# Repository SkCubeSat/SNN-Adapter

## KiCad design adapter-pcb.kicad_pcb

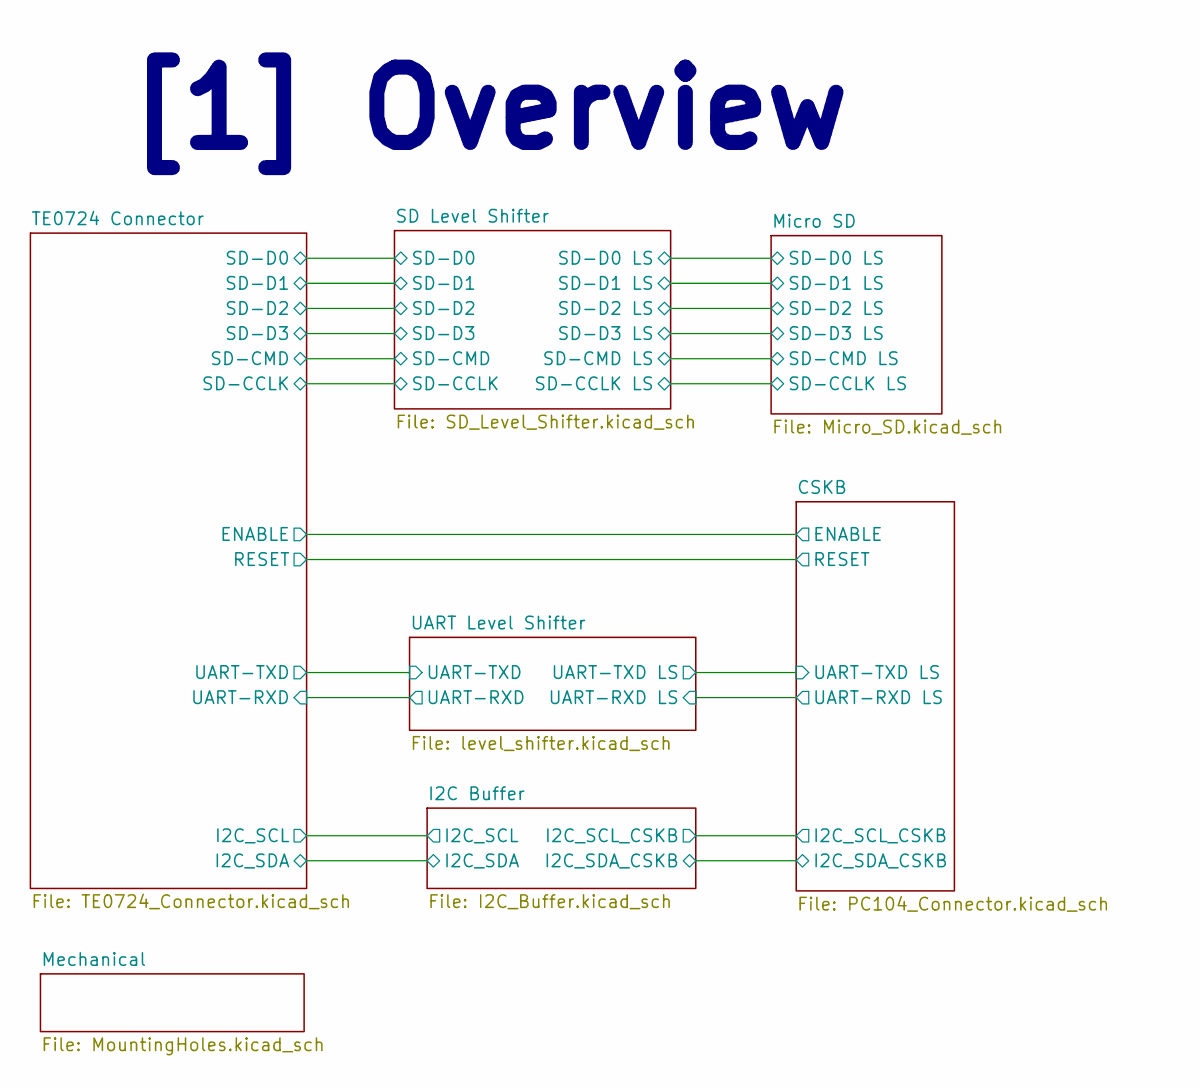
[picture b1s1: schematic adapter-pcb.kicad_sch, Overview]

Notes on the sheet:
[1] Overview

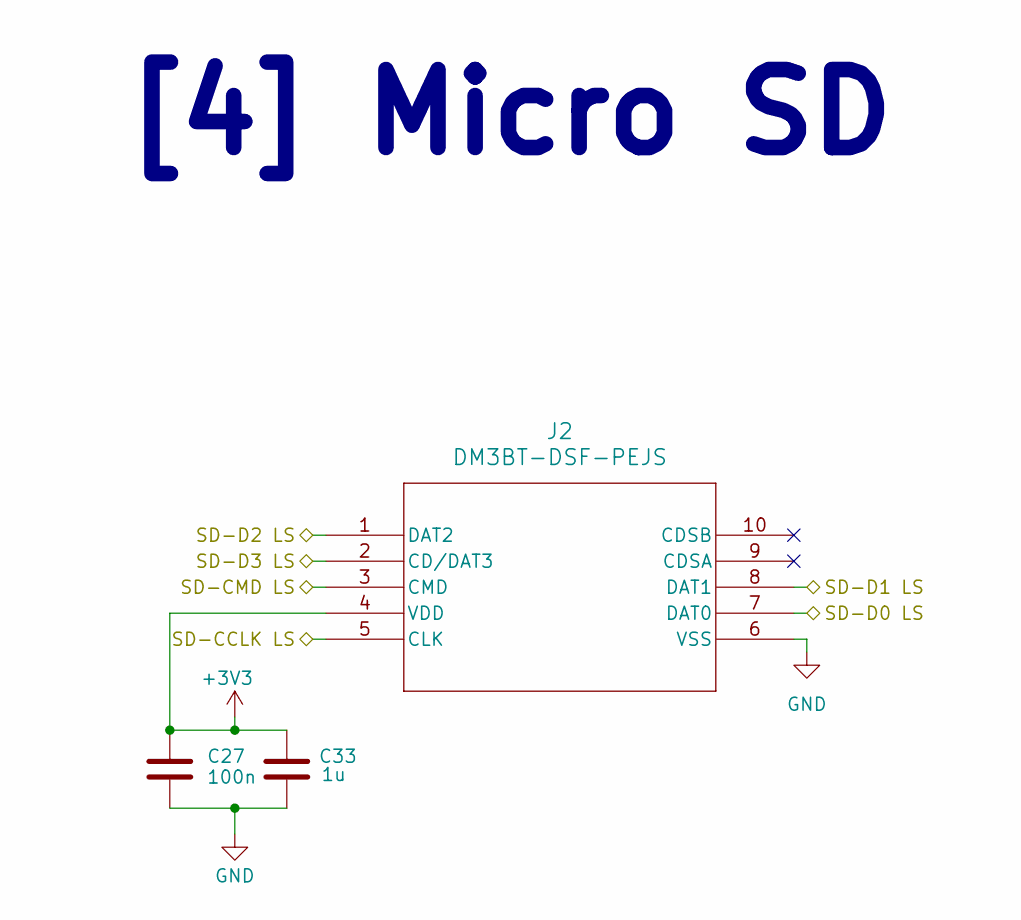
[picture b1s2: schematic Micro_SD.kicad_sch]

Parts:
C27: 100n; C_0603_1608Metric; MPN GCM188R71H104KA57J
C33: 1u; C_0805_2012Metric; MPN GCM21BR71H105KA03L
J2: DM3BT-DSF-PEJS; DM3BT_DSF_PEJS; MPN DM3BT-DSF-PEJS

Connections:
+3V3: C27.1, C33.1, J2.4 (VDD); also elsewhere on the board
/Micro SD/SD-CCLK LS: J2.5 (CLK); also elsewhere on the board
/Micro SD/SD-CMD LS: J2.3 (CMD); also elsewhere on the board
/Micro SD/SD-D0 LS: J2.7 (DAT0); also elsewhere on the board
/Micro SD/SD-D1 LS: J2.8 (DAT1); also elsewhere on the board
/Micro SD/SD-D2 LS: J2.1 (DAT2); also elsewhere on the board
/Micro SD/SD-D3 LS: J2.2 (CD/DAT3); also elsewhere on the board
GND: C27.2, C33.2, J2.6 (VSS); also elsewhere on the board

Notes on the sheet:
[4] Micro SD

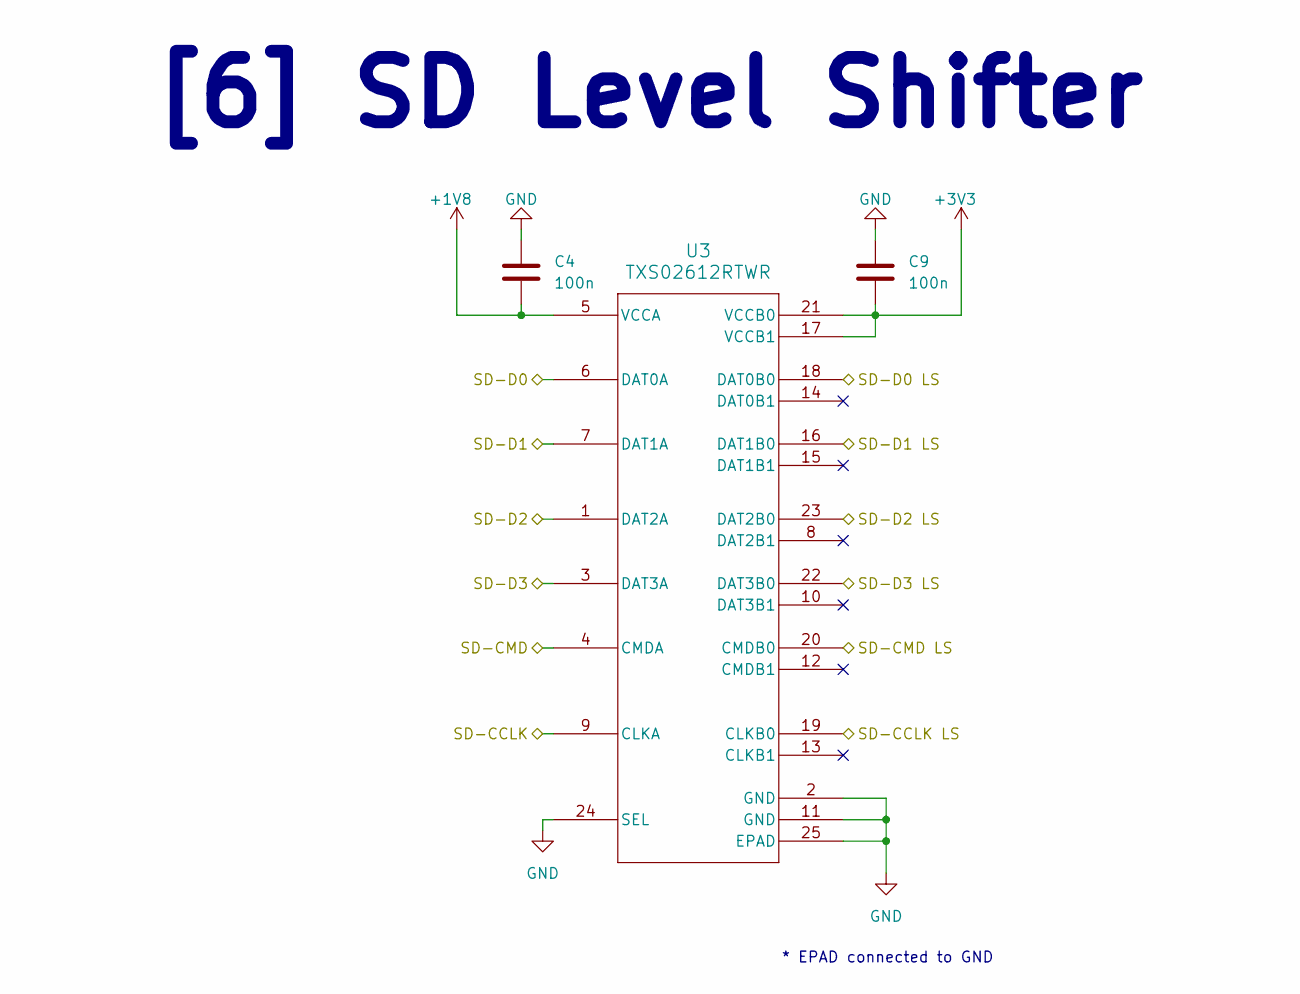
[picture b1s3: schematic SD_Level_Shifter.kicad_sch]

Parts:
C4, C9: 100n; C_0603_1608Metric; MPN GCM188R71H104KA57J
U3: TXS02612RTWR; RTW24_2P45X2P45; MPN TXS02612RTWR

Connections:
+1V8: C4.2, U3.5 (VCCA); also elsewhere on the board
+3V3: C9.2, U3.17 (VCCB1), U3.21 (VCCB0); also elsewhere on the board
/Micro SD/SD-CCLK LS: U3.19 (CLKB0); also elsewhere on the board
/Micro SD/SD-CMD LS: U3.20 (CMDB0); also elsewhere on the board
/Micro SD/SD-D0 LS: U3.18 (DAT0B0); also elsewhere on the board
/Micro SD/SD-D1 LS: U3.16 (DAT1B0); also elsewhere on the board
/Micro SD/SD-D2 LS: U3.23 (DAT2B0); also elsewhere on the board
/Micro SD/SD-D3 LS: U3.22 (DAT3B0); also elsewhere on the board
/SD Level Shifter/SD-CCLK: U3.9 (CLKA); also elsewhere on the board
/SD Level Shifter/SD-CMD: U3.4 (CMDA); also elsewhere on the board
/SD Level Shifter/SD-D0: U3.6 (DAT0A); also elsewhere on the board
/SD Level Shifter/SD-D1: U3.7 (DAT1A); also elsewhere on the board
/SD Level Shifter/SD-D2: U3.1 (DAT2A); also elsewhere on the board
/SD Level Shifter/SD-D3: U3.3 (DAT3A); also elsewhere on the board
GND: C4.1, C9.1, U3.2 (GND), U3.11 (GND), U3.24 (SEL), U3.25 (EPAD); also elsewhere on the board

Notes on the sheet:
[6] SD Level Shifter
* EPAD connected to GND

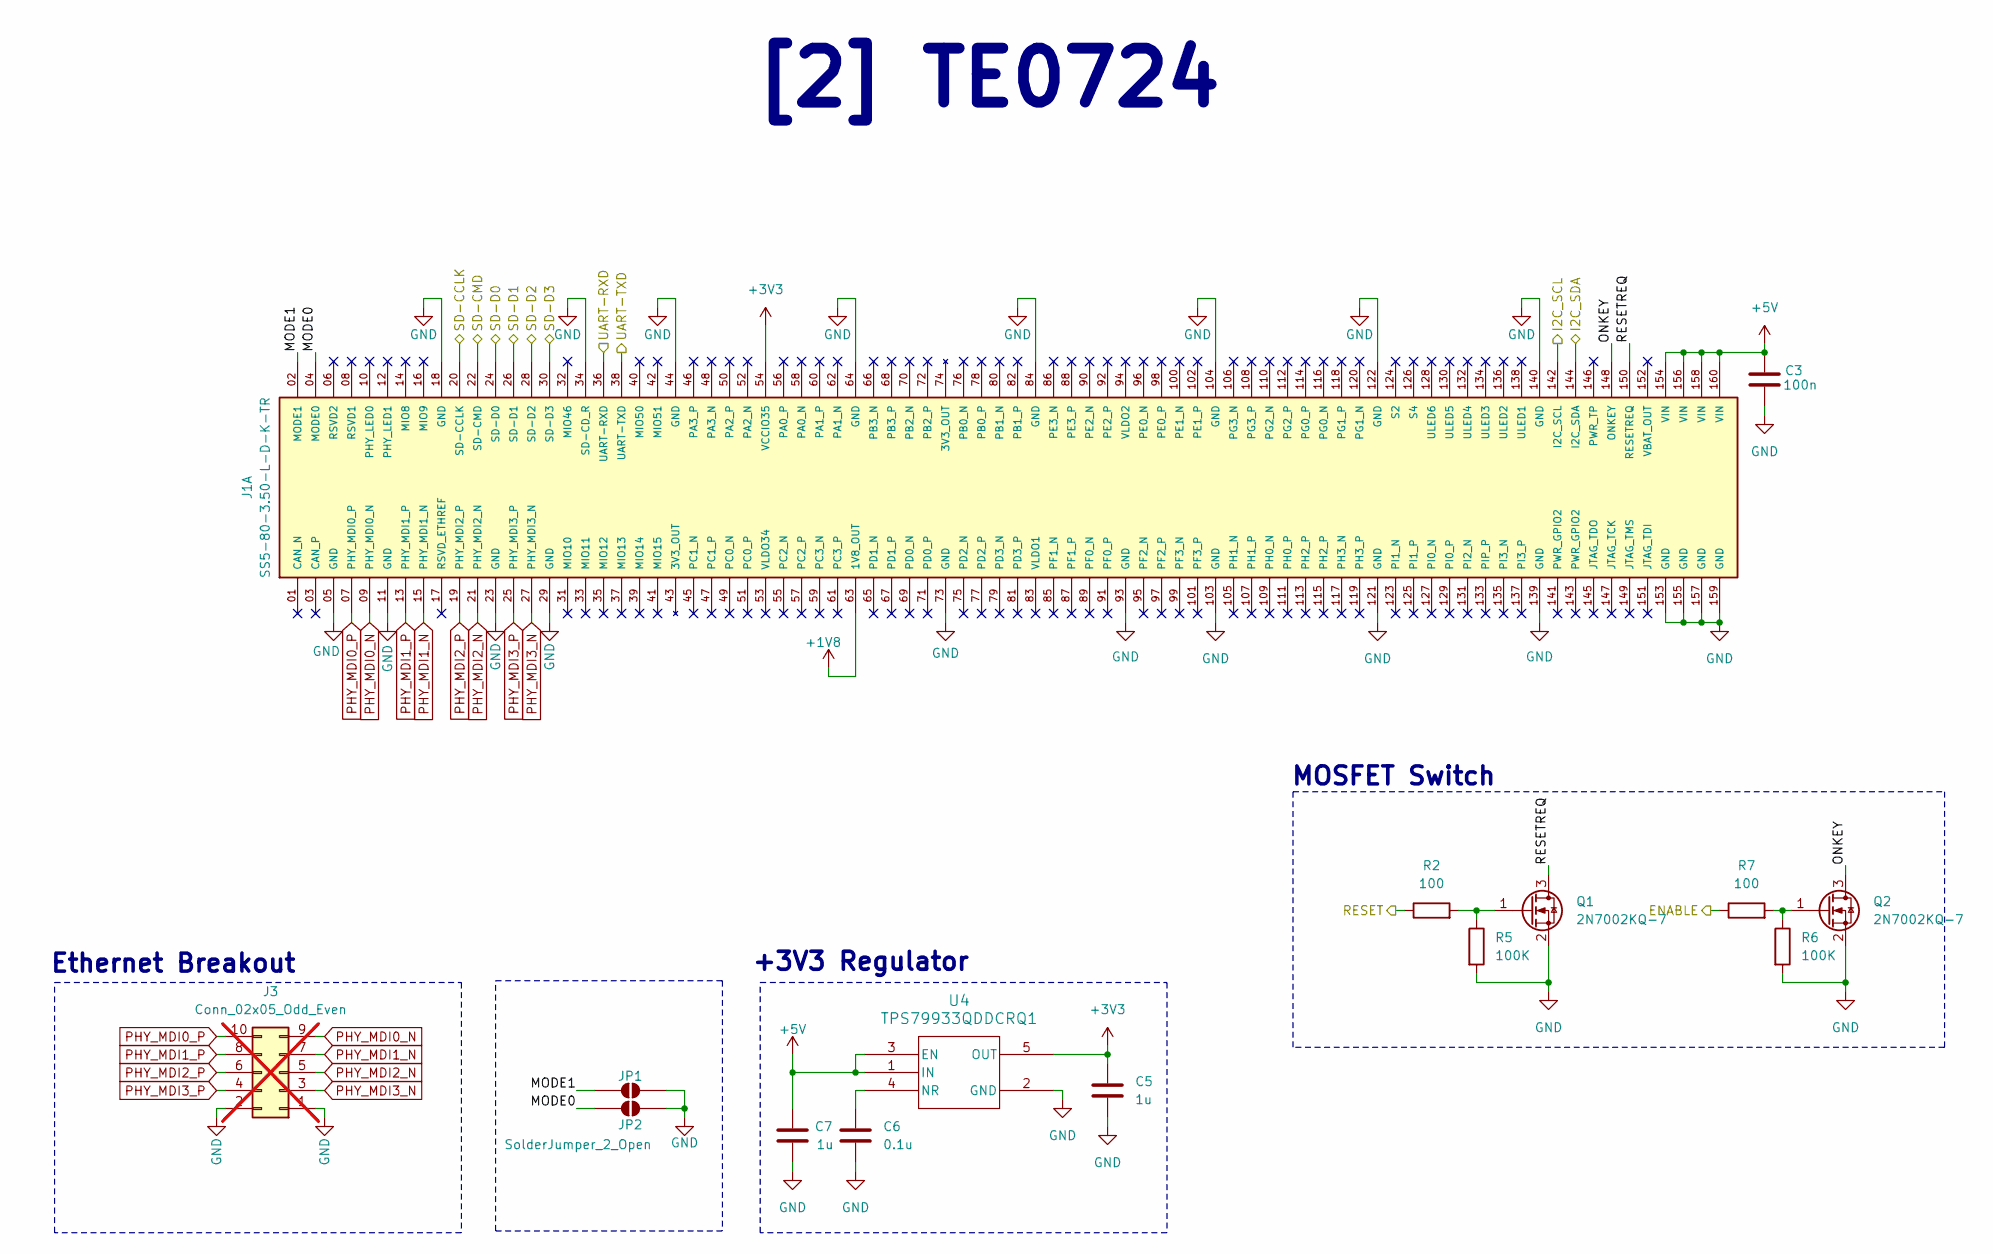
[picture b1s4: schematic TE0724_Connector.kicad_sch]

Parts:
C3: 100n; C_0603_1608Metric; MPN GCM188R71H104KA57J
C5, C7: 1u; C_1206_3216Metric; MPN GCM31MR71H105KA55L
C6: 0.1u; C_0603_1608Metric; MPN GCM188R71H104KA57J
J1: SS5-80-3.50-L-D-K-TR; SAMTEC_SS5-80-3.50-X-D-K-XX; PARTREV F
J3: Conn_02x05_Odd_Even; PinSocket_2x05_P2.54mm_Vertical; not fitted
JP1, JP2: SolderJumper_2_Open; SolderJumper-2_P1.3mm_Open_RoundedPad1.0x1.5mm
Q1, Q2: 2N7002KQ-7; SOT-23; MPN 2N7002KQ-7
R2, R7: 100; R_0402_1005Metric; MPN MCS0402MD1000BE100
R5, R6: 100K; R_0402_1005Metric; MPN MCS0402MD1003BE100
U4: TPS79933QDDCRQ1; DDC5; MPN TPS79933QDDCRQ1

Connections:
+1V8: J1.63 (1V8_OUT); also elsewhere on the board
+3V3: C5.1, J1.54 (VCCIO35), U4.5 (OUT); also elsewhere on the board
+5V: C3.1, C7.1, J1.154 (VIN), J1.156 (VIN), J1.158 (VIN), J1.160 (VIN), U4.1 (IN), U4.3 (EN); also elsewhere on the board
/CSKB/ENABLE: R7.1; also elsewhere on the board
/CSKB/RESET: R2.1; also elsewhere on the board
/I2C Buffer/I2C_SCL: J1.142 (I2C_SCL); also elsewhere on the board
/I2C Buffer/I2C_SDA: J1.144 (I2C_SDA); also elsewhere on the board
/SD Level Shifter/SD-CCLK: J1.20 (SD-CCLK); also elsewhere on the board
/SD Level Shifter/SD-CMD: J1.22 (SD-CMD); also elsewhere on the board
/SD Level Shifter/SD-D0: J1.24 (SD-D0); also elsewhere on the board
/SD Level Shifter/SD-D1: J1.26 (SD-D1); also elsewhere on the board
/SD Level Shifter/SD-D2: J1.28 (SD-D2); also elsewhere on the board
/SD Level Shifter/SD-D3: J1.30 (SD-D3); also elsewhere on the board
/TE0724 Connector/MODE0: J1.04 (MODE0), JP2.1 (A)
/TE0724 Connector/MODE1: J1.02 (MODE1), JP1.1 (A)
/TE0724 Connector/ONKEY: J1.148 (ONKEY), Q2.3 (D)
/TE0724 Connector/RESETREQ: J1.150 (RESETREQ), Q1.3 (D)
/TE0724 Connector/UART-RXD: J1.36 (UART-RXD); also elsewhere on the board
/TE0724 Connector/UART-TXD: J1.38 (UART-TXD); also elsewhere on the board
GND: C3.2, C5.2, C6.2, C7.2, J1.05 (GND), J1.11 (GND), J1.18 (GND), J1.23 (GND), J1.29 (GND), J1.34 (SD-CD_R), J1.44 (GND), J1.64 (GND), J1.73 (GND), J1.84 (GND), J1.93 (GND), J1.103 (GND), J1.104 (GND), J1.121 (GND), J1.122 (GND), J1.139 (GND), J1.140 (GND), J1.153 (GND), J1.155 (GND), J1.157 (GND), J1.159 (GND), J3.1, J3.2, JP1.2 (B), JP2.2 (B), Q1.2 (S), Q2.2 (S), R5.2, R6.2, U4.2 (GND); also elsewhere on the board
unnamed: Q1.1 (G), R2.2, R5.1
unnamed: Q2.1 (G), R6.1, R7.2
unnamed: C6.1, U4.4 (NR)
PHY_MDI0_N: J1.09 (PHY_MDI0_N), J3.9
PHY_MDI0_P: J1.07 (PHY_MDI0_P), J3.10
PHY_MDI1_N: J1.15 (PHY_MDI1_N), J3.7
PHY_MDI1_P: J1.13 (PHY_MDI1_P), J3.8
PHY_MDI2_N: J1.21 (PHY_MDI2_N), J3.5
PHY_MDI2_P: J1.19 (PHY_MDI2_P), J3.6
PHY_MDI3_N: J1.27 (PHY_MDI3_N), J3.3
PHY_MDI3_P: J1.25 (PHY_MDI3_P), J3.4

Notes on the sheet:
+3V3 Regulator
MOSFET Switch
[2] TE0724
Ethernet Breakout

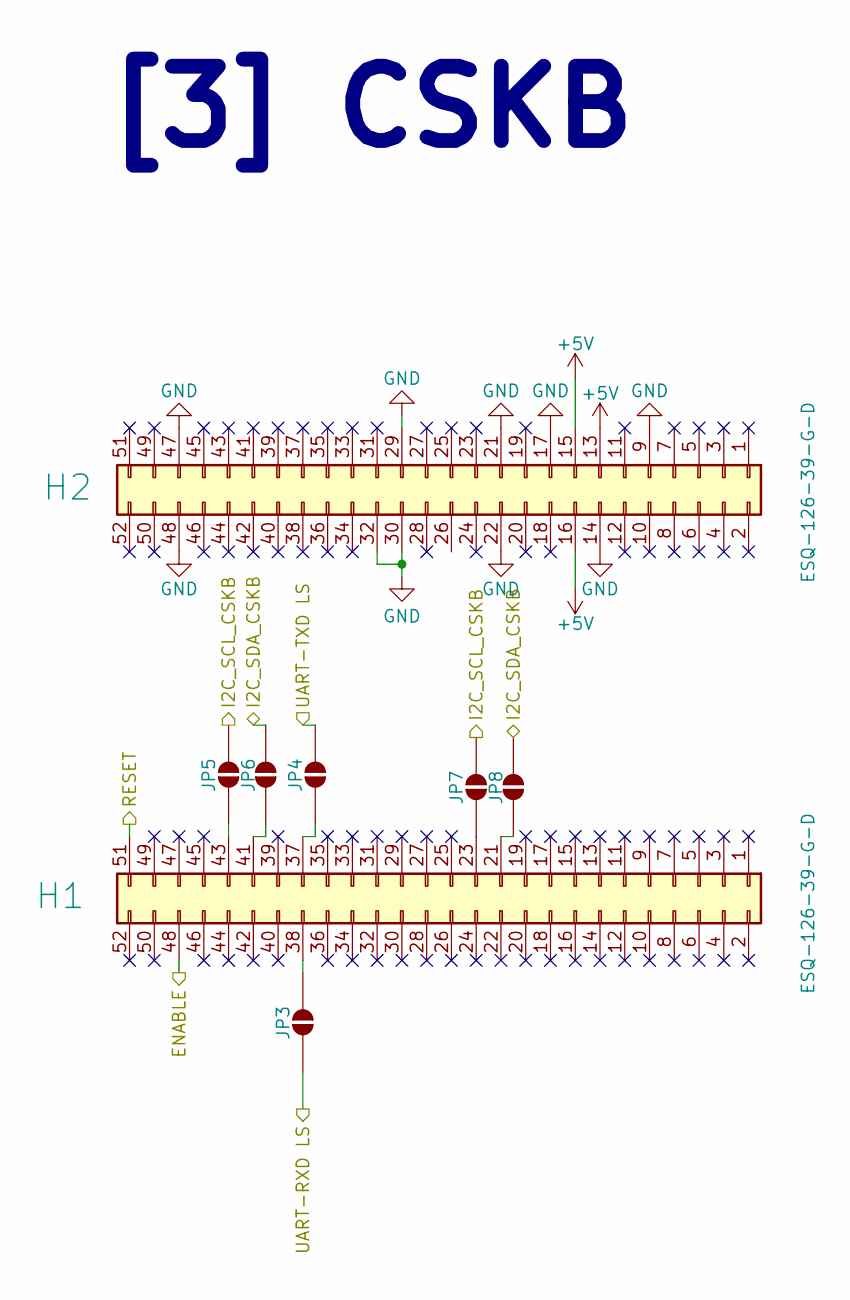
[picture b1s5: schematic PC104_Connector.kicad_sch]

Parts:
H1, H2: ESQ-126-39-G-D; RHDR52W64P254_2X26_6654X495X1135P; MPN ESQ-126-39-G-D
JP3, JP4: SolderJumper_2_Open; SolderJumper-2_P1.3mm_Bridged_RoundedPad1.0x1.5mm
JP5, JP6, JP7, JP8: SolderJumper_2_Open; SolderJumper-2_P1.3mm_Open_RoundedPad1.0x1.5mm

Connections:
+5V: H2.13, H2.15, H2.16; also elsewhere on the board
/CSKB/ENABLE: H1.48; also elsewhere on the board
/CSKB/I2C_SCL_CSKB: JP5.2 (B), JP7.2 (B); also elsewhere on the board
/CSKB/I2C_SDA_CSKB: JP6.2 (B), JP8.2 (B); also elsewhere on the board
/CSKB/RESET: H1.51; also elsewhere on the board
/CSKB/UART-RXD LS: JP3.1 (A); also elsewhere on the board
/CSKB/UART-TXD LS: JP4.2 (B); also elsewhere on the board
GND: H2.9, H2.14, H2.17, H2.21, H2.22, H2.29, H2.30, H2.32, H2.47, H2.48; also elsewhere on the board
unnamed: H1.21, JP8.1 (A)
unnamed: H1.23, JP7.1 (A)
unnamed: H1.37, JP4.1 (A)
unnamed: H1.38, JP3.2 (B)
unnamed: H1.41, JP6.1 (A)
unnamed: H1.43, JP5.1 (A)

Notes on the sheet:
[3] CSKB

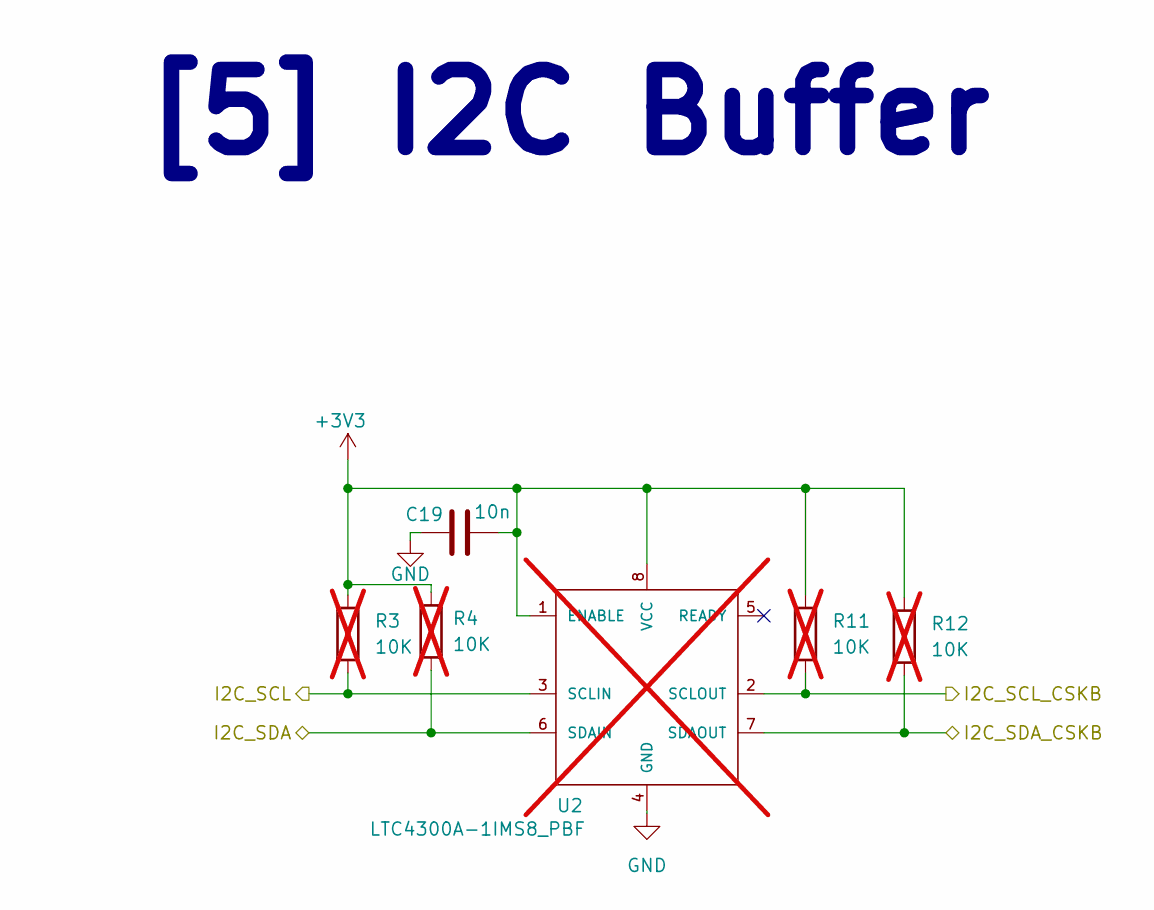
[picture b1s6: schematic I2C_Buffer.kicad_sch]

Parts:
C19: 10n; C_0402_1005Metric; MPN GCM155R71H103KA55J
R3, R4, R11, R12: 10K; R_0402_1005Metric; MPN MCS0402MD1002BE100; not fitted
U2: LTC4300A-1IMS8_PBF; MPN ltc4300a1ims8; not fitted

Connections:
+3V3: C19.2, R3.1, R4.1, R11.1, R12.1, U2.1 (ENABLE), U2.8 (VCC); also elsewhere on the board
/CSKB/I2C_SCL_CSKB: R11.2, U2.2 (SCLOUT); also elsewhere on the board
/CSKB/I2C_SDA_CSKB: R12.2, U2.7 (SDAOUT); also elsewhere on the board
/I2C Buffer/I2C_SCL: R3.2, U2.3 (SCLIN); also elsewhere on the board
/I2C Buffer/I2C_SDA: R4.2, U2.6 (SDAIN); also elsewhere on the board
GND: C19.1, U2.4 (GND); also elsewhere on the board

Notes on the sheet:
[5] I2C Buffer

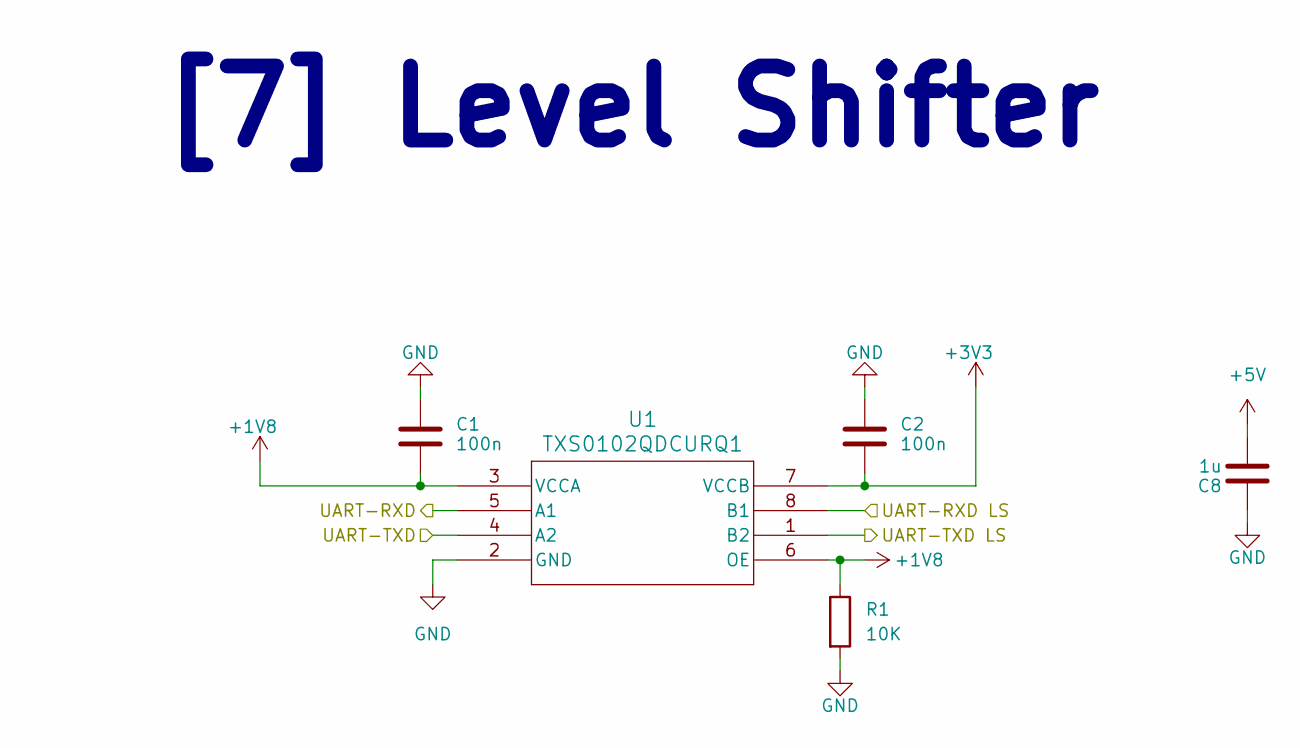
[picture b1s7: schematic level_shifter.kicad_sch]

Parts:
C1, C2: 100n; C_0603_1608Metric; MPN GCM188R71H104KA57J
C8: 1u; C_0603_1608Metric; MPN GCM188R71E105KA64D
R1: 10K; R_0402_1005Metric; MPN MCS0402MD1002BE100
U1: TXS0102QDCURQ1; MPN TXS0102QDCURQ1

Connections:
+1V8: C1.2, R1.1, U1.3 (VCCA), U1.6 (OE); also elsewhere on the board
+3V3: C2.2, U1.7 (VCCB); also elsewhere on the board
+5V: C8.2; also elsewhere on the board
/CSKB/UART-RXD LS: U1.8 (B1); also elsewhere on the board
/CSKB/UART-TXD LS: U1.1 (B2); also elsewhere on the board
/TE0724 Connector/UART-RXD: U1.5 (A1); also elsewhere on the board
/TE0724 Connector/UART-TXD: U1.4 (A2); also elsewhere on the board
GND: C1.1, C2.1, C8.1, R1.2, U1.2 (GND); also elsewhere on the board

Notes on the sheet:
[7] Level Shifter

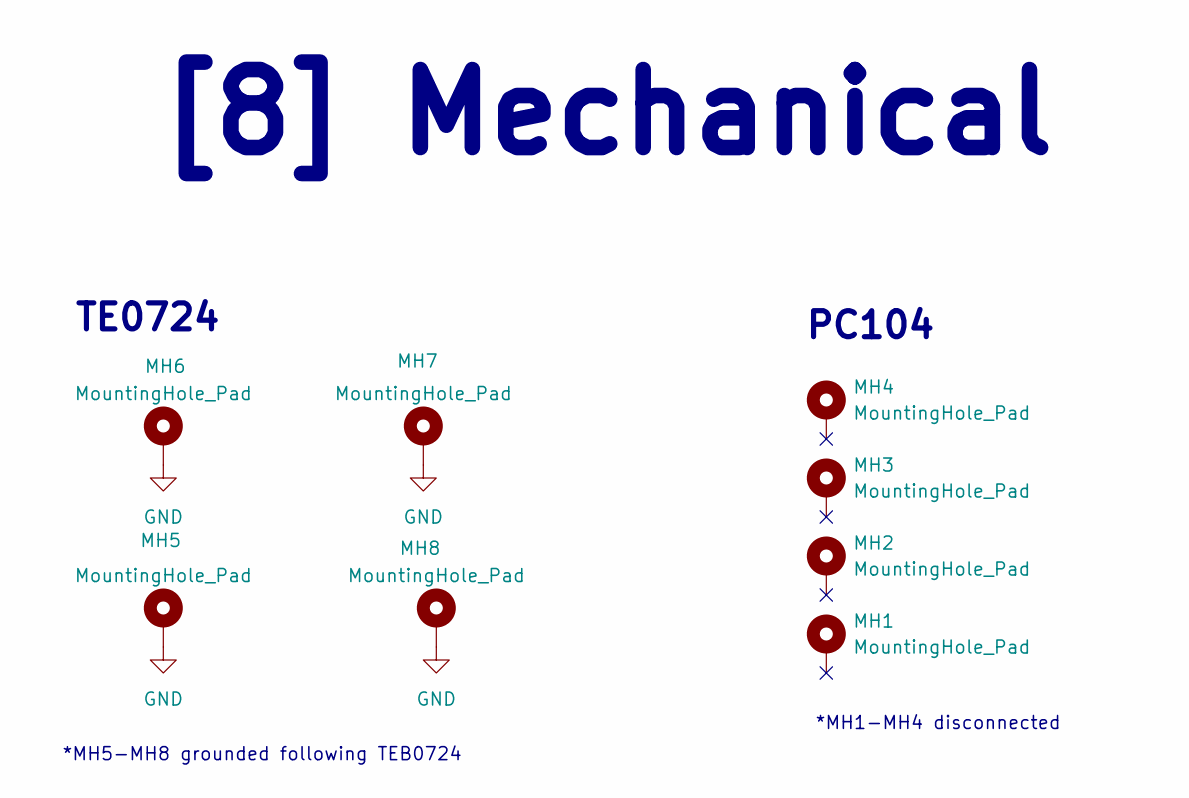
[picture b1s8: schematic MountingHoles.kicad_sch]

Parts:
MH1, MH2, MH3, MH4: MountingHole_Pad; MountingHole_3.18mm_6.35mm_Pad
MH5, MH6, MH7, MH8: MountingHole_Pad; MountingHole_2.2mm_M2_Pad

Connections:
GND: MH5.1 (1_1), MH6.1 (1_1), MH7.1 (1_1), MH8.1 (1_1); also elsewhere on the board

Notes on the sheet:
PC104
*MH1-MH4 disconnected
[8] Mechanical
TE0724
*MH5-MH8 grounded following TEB0724

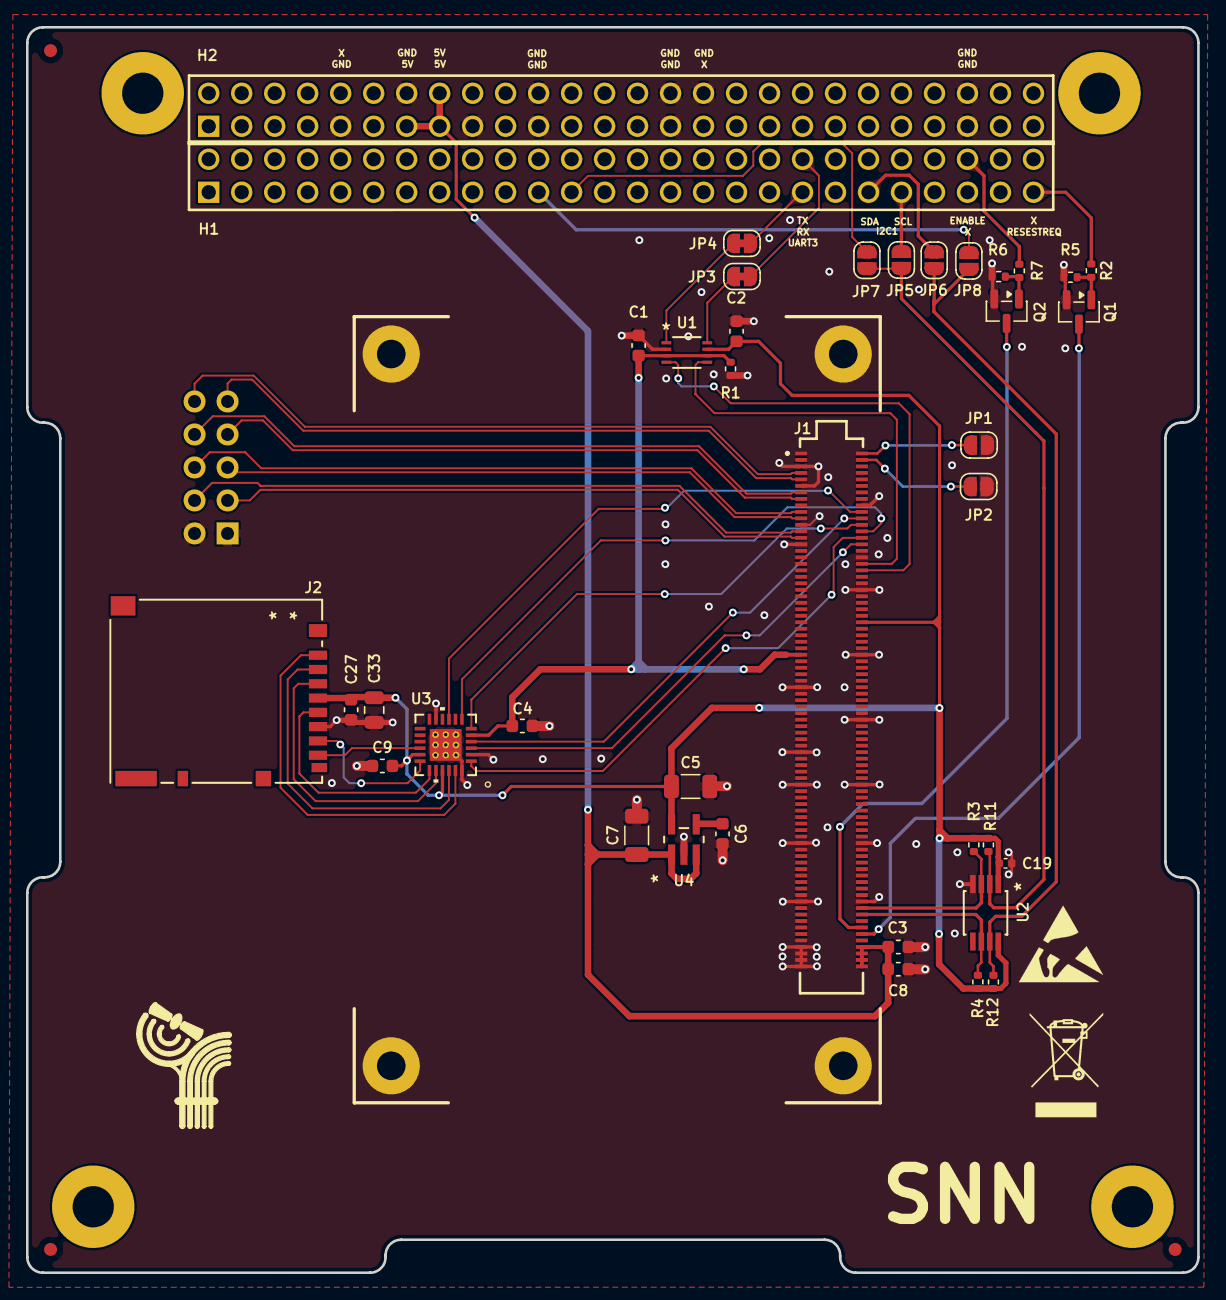
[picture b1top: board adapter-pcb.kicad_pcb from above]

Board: 2 copper layers, 90.2 x 95.9 mm, 48 parts (1 on the bottom side), 47 nets.

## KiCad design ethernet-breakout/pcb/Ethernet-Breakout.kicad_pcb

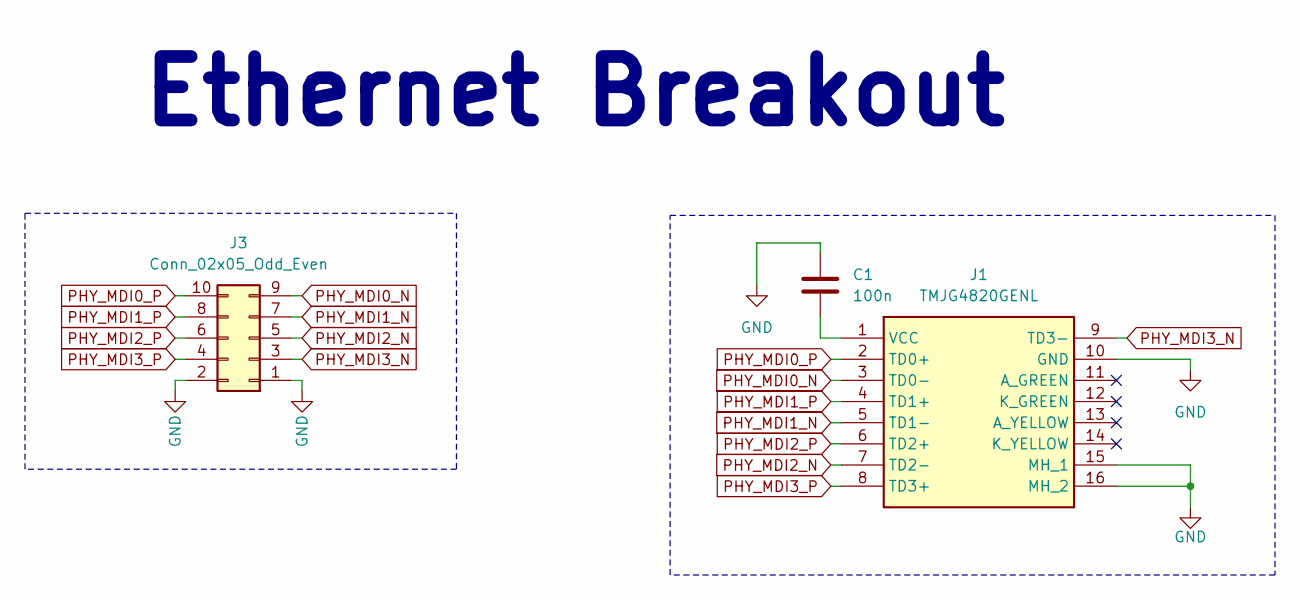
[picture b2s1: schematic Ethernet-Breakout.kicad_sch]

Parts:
C1: 100n; C_Disc_D3.0mm_W1.6mm_P2.50mm
J1: TMJG4820GENL; Mouser Part Number 960-TMJG4820GENL
J3: Conn_02x05_Odd_Even; PinSocket_2x05_P2.54mm_Vertical

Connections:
GND: C1.1, J1.10 (GND), J1.15 (MH_1), J1.16 (MH_2), J3.1, J3.2
unnamed: C1.2, J1.1 (VCC)
PHY_MDI0_N: J1.3 (TD0-), J3.9
PHY_MDI0_P: J1.2 (TD0+), J3.10
PHY_MDI1_N: J1.5 (TD1-), J3.7
PHY_MDI1_P: J1.4 (TD1+), J3.8
PHY_MDI2_N: J1.7 (TD2-), J3.5
PHY_MDI2_P: J1.6 (TD2+), J3.6
PHY_MDI3_N: J1.9 (TD3-), J3.3
PHY_MDI3_P: J1.8 (TD3+), J3.4

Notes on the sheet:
Ethernet Breakout

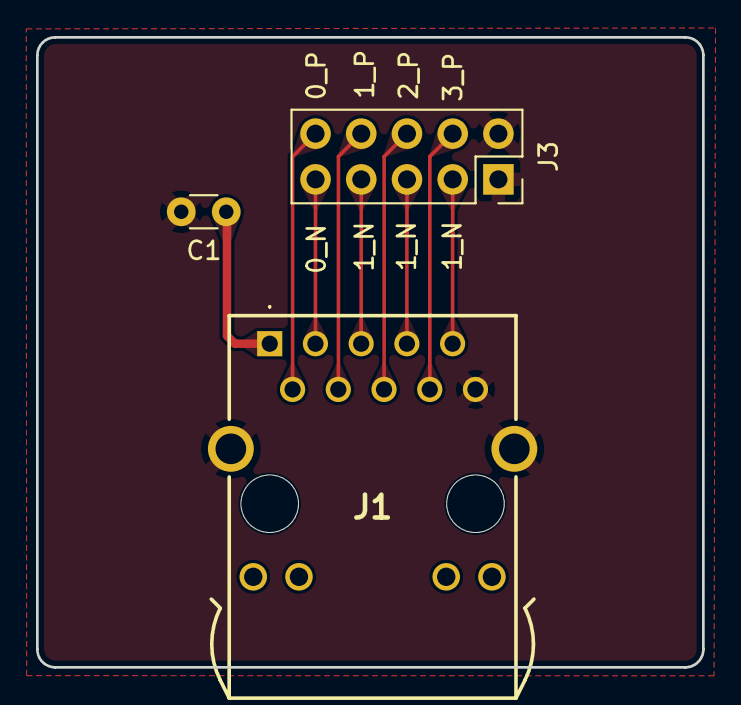
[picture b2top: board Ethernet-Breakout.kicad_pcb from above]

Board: 2 copper layers, 37.0 x 35.0 mm, 3 parts (0 on the bottom side), 10 nets.

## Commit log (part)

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2026-02-08 Routed PCB (with I2C buffer)
2026-02-09 fixed and labeled CSKB header, added 3D models
2026-02-15 Fixed GND issues with connector and mounting holes
2026-05-02 Added some decoup caps and reviewed PCB layout
2026-05-03 removed some decoup caps because I added to many haha
2026-05-04 Added Level Shifter for SD card
2026-05-05 Rerouted SD a little bit
2026-05-05 Rerouted 3V3 trace
2026-05-07 moved vias farther from pads
2026-05-10 Added pcb files for ethernet breakout board
2026-05-17 Updated BOM and added fiducials
2026-05-30 Changed connector orientation and power changes
2026-05-30 reviewed changes to PCB
2026-05-31 added mroe GND pins and moved power to PDM lines
2026-05-31 Made very tiny tweaks
2026-05-31 Made very tiny tweaks again
2026-06-03 added solder bridges and updated BOM
